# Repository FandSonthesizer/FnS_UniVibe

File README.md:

# FnS_UniVibe

A Univibe Clone using a white LED. This is a modern version of a univibe clone, instead of using a 15V lamp we use a white LED. This requested to modify the lamp driver circuit so now a dual opamp is driving it. We are using LDR03 for the light depending resistors, but a wide variety of LDRs will work too. Any standard Dual-Opamp will do.

The LDR's are so sensitive, that we have to dim the white LED quite a lot. A 47k resistor just brings the brightness down enough. Who would have thought... This should really bring down the power consumption compared to the original module.

Adapt the circuit to other LDR's by playing around with R58.

Check out our youtube channel: FatherandSonthesizer for a detailed demo of this cool module. (Though we use it in a synth rack...)

The PCB is prepared for the Vodoovibe and Resley Tone mod. Just do not populate C7, C12, C16 and C19. Instead follow the second link on the schematic and wire the caps on the 4P3T switch. connect using J12 and an 8pol cable. If you do not want the mod, ignore J12 and just populate the board as shown in the schematic.

Please note, that we forgot the true bypass switch on our front panel design. Maybe someone can come up with a better design, we would love to include it here.

The output signal of the module is somewhat less in volume than the input signal. A 2nd opamp takes care of that. A potentiometer on the front panel allows to adjust that volume.

For the led, LDR combination we created a symbol and a foot print for Kicad. Both are included in this repository. Make sure to configure your Kicad to make use of them. That symbol is called FnSVibeC, the foot print is in the NilsParts.pretty lib. Since no ambient light should reach the foto resistors we used a 3d-printer to print a housing for this part. Just a hollow square box, useing black PLA. (1mm wall)

The sound of this module is just awsome, make sure to check out youtube video. A guitar pedal version will follow later.

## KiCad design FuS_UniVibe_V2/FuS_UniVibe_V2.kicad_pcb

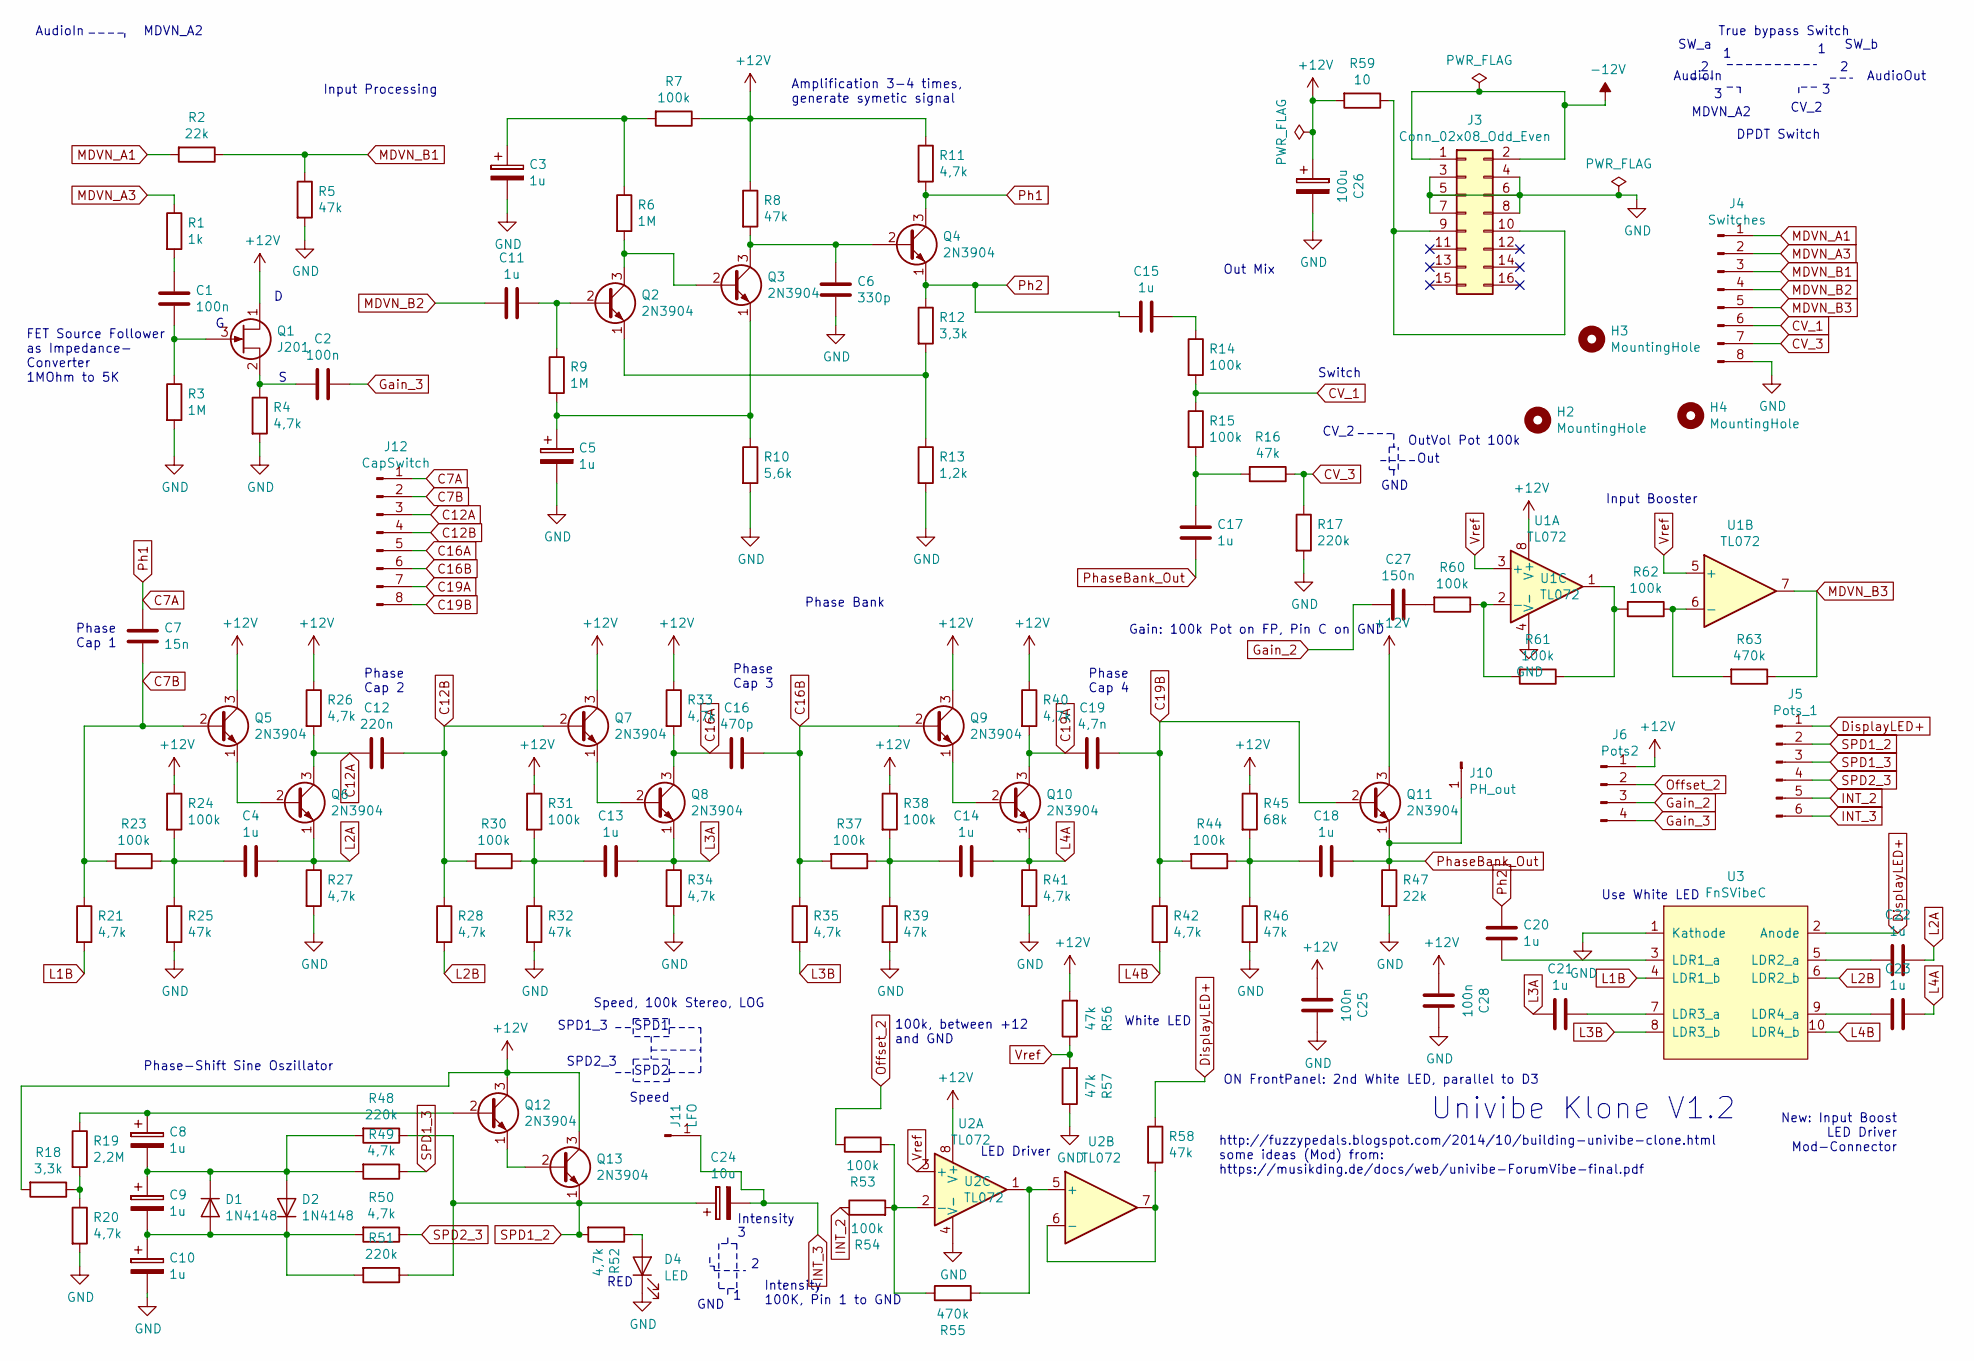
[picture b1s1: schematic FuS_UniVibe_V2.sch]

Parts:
C1, C2, C25, C28: 100n; Kondensator_Keramik
C3, C5, C8, C9, C10: 1u; Elko_D6.3mm_P2.50mm
C4, C11, C13, C14, C15, C17, C18, C20, C21, C22, C23: 1u; BIPolar_Elko_D6.3mm_P2.50mm
C6: 330p; Kondensator_Keramik
C7: 15n; Kondensator_Keramik
C12: 220n; Kondensator_Keramik
C16: 470p; Kondensator_Keramik
C19: 4,7n; Kondensator_Keramik
C24: 10u; Elko_D6.3mm_P2.50mm
C26: 100u; Elko_D6.3mm_P2.50mm
C27: 150n; Kondensator_Keramik
D1, D2: 1N4148; Diode_Horizontal
D4: LED; LED_Vertikal
H2, H3, H4: MountingHole; MountHole
J3: Conn_02x08_Odd_Even; PinHeader_2x08_P2.54mm_Vertical
J4: Switches; PinHeader_1x08_P2.54mm_Vertical
J5: Pots_1; PinHeader_1x06_P2.54mm_Vertical
J6: Pots2; PinHeader_1x04_P2.54mm_Vertical
J10: PH_out; Stift
J11: LFO; Stift
J12: CapSwitch; PinHeader_1x08_P2.54mm_Vertical
Q1: J201; TO-92_Wide
Q2, Q3, Q4, Q5, Q6, Q7, Q8, Q9, Q10, Q11, Q12, Q13: 2N3904; TO-92_Wide
R1: 1k; Widerstand_liegend
R2, R47: 22k; Widerstand_liegend
R3, R6, R9: 1M; Widerstand_liegend
R4, R11, R20, R21, R26, R27, R28, R33, R34, R35, R40, R41, R42, R49, R50, R52: 4,7k; Widerstand_liegend
R5, R8, R16, R25, R32, R39, R46, R56, R57, R58: 47k; Widerstand_liegend
R7, R14, R15, R23, R24, R30, R31, R37, R38, R44, R53, R54, R60, R61, R62: 100k; Widerstand_liegend
R10: 5,6k; Widerstand_liegend
R12, R18: 3,3k; Widerstand_liegend
R13: 1,2k; Widerstand_liegend
R17, R48, R51: 220k; Widerstand_liegend
R19: 2,2M; Widerstand_liegend
R45: 68k; Widerstand_liegend
R55, R63: 470k; Widerstand_liegend
R59: 10; Widerstand_liegend
U1, U2: TL072; DIP-8_W7.62mm_Socket_LongPads
U3: FnSVibeC; FnSVibe

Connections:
+12V: C25.2, C26.1, C28.2, J6.1, Q1.1 (D), Q5.3 (C), Q7.3 (C), Q9.3 (C), Q11.3 (C), Q12.3 (C), Q13.3 (C), R7.1, R8.1, R11.1, R18.2, R24.1, R26.1, R31.1, R33.1, R38.1, R40.1, R45.1, R56.2, R59.2, U1.8 (V+), U2.8 (V+)
-12V: J3.1, J3.2
C7A: C7.1, J12.1, Q4.3 (C), R11.2
C7B: C7.2, J12.2, Q5.2 (B), R21.1, R23.2
C12A: C12.2, J12.3, Q6.3 (C), R26.2
C12B: C12.1, J12.4, Q7.2 (B), R28.1, R30.2
C16A: C16.2, J12.5, Q8.3 (C), R33.2
C16B: C16.1, J12.6, Q9.2 (B), R35.1, R37.2
C19A: C19.2, J12.7, Q10.3 (C), R40.2
C19B: C19.1, J12.8, Q11.2 (B), R42.1, R44.2
CV_1: J4.6, R14.2, R15.1
CV_3: J4.7, R16.1, R17.1
DisplayLED+: J5.1, R58.1, U3.2 (Anode)
GND: C3.2, C5.2, C6.2, C10.2, C25.1, C26.2, C28.1, D4.1 (K), J3.3, J3.4, J3.5, J3.6, J3.7, J3.8, J4.8, R3.2, R4.2, R5.2, R10.2, R13.2, R17.2, R20.2, R25.2, R27.2, R32.2, R34.2, R39.2, R41.2, R46.2, R47.2, R57.1, U1.4 (V-), U2.4 (V-), U3.1 (Kathode)
Gain_2: C27.2, J6.3
Gain_3: C2.1, J6.4
INT_2: J5.5, R54.1
INT_3: C24.2, J5.6, J11.1
L1B: R21.2, U3.4 (LDR1_b)
L2A: C4.1, C22.2, Q6.1 (E), R27.1
L2B: R28.2, U3.6 (LDR2_b)
L3A: C13.1, C21.1, Q8.1 (E), R34.1
L3B: R35.2, U3.8 (LDR3_b)
L4A: C14.1, C23.2, Q10.1 (E), R41.1
L4B: R42.2, U3.10 (LDR4_b)
MDVN_A1: J4.1, R2.2
MDVN_A3: J4.2, R1.1
MDVN_B1: J4.3, R2.1, R5.1
MDVN_B2: C11.2, J4.4
MDVN_B3: J4.5, R63.1, U1.7
unnamed: C1.1, R1.2
unnamed: C1.2, Q1.3 (G), R3.1
unnamed: C2.2, Q1.2 (S), R4.1
unnamed: C3.1, R6.1, R7.2
unnamed: C4.2, R23.1, R24.2, R25.1
unnamed: C5.1, Q3.1 (E), R9.2, R10.1
unnamed: C6.1, Q3.3 (C), Q4.2 (B), R8.2
unnamed: C8.1, Q12.2 (B), R19.1
unnamed: C8.2, C9.1, D1.1 (K), D2.2 (A), R48.2, R49.2
unnamed: C9.2, C10.1, D1.2 (A), D2.1 (K), R50.2, R51.2
unnamed: C11.1, Q2.2 (B), R9.1
unnamed: C13.2, R30.1, R31.2, R32.1
unnamed: C14.2, R37.1, R38.2, R39.1
unnamed: C15.1, R14.1
unnamed: C17.2, R15.2, R16.2
unnamed: C18.2, R44.1, R45.2, R46.1
unnamed: C20.1, U3.3 (LDR1_a)
unnamed: C21.2, U3.7 (LDR3_a)
unnamed: C22.1, U3.5 (LDR2_a)
unnamed: C23.1, U3.9 (LDR4_a)
unnamed: C27.1, R60.2
unnamed: D4.2 (A), R52.1
unnamed: J3.9, J3.10, R59.1
unnamed: Q2.1 (E), R12.2, R13.1
unnamed: Q2.3 (C), Q3.2 (B), R6.2
unnamed: Q5.1 (E), Q6.2 (B)
unnamed: Q7.1 (E), Q8.2 (B)
unnamed: Q9.1 (E), Q10.2 (B)
unnamed: Q12.1 (E), Q13.2 (B)
unnamed: R18.1, R19.2, R20.1
unnamed: R53.2, R54.2, R55.1, U2.2 (-)
unnamed: R55.2, U2.1, U2.5 (+)
unnamed: R58.2, U2.6 (-), U2.7
unnamed: R60.1, R61.2, U1.2 (-)
unnamed: R61.1, R62.2, U1.1
unnamed: R62.1, R63.2, U1.6 (-)
Offset_2: J6.2, R53.1
Ph2: C15.2, C20.2, Q4.1 (E), R12.1
PhaseBank_Out: C17.1, C18.1, J10.1, Q11.1 (E), R47.1
SPD1_2: C24.1, J5.2, Q13.1 (E), R48.1, R51.1, R52.2
SPD1_3: J5.3, R49.1
SPD2_3: J5.4, R50.1
Vref: R56.1, R57.2, U1.3 (+), U1.5 (+), U2.3 (+)

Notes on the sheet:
AudioIn
MDVN_A2
CV_2
GND
Out
OutVol Pot 100k
Input Processing
Out Mix
Phase Bank
Phase-Shift Sine Oszillator
SPD1
SPD2
SPD1_3
SPD2_3
Speed, 100k Stereo, LOG
Intensity 100K, Pin 1 to GND
Switch
Univibe Klone V1.2
http://fuzzypedals.blogspot.com/2014/10/building-univibe-clone.html some ideas (Mod) from: https://musikding.de/docs/web/univibe-ForumVibe-final.pdf
White LED
Speed
FET Source Follower as Impedance- Converter 1MOhm to 5K
Amplification 3-4 times, generate symetic signal
Phase Cap 1
Phase Cap 2
Phase Cap 3
Phase Cap 4
Intensity
100k, between +12 and GND
ON FrontPanel: 2nd White LED, parallel to D3
RED
True bypass Switch
SW_a
SW_b
DPDT Switch
AudioOut
Input Booster
Gain: 100k Pot on FP, Pin C on GND
New: Input Boost LED Driver Mod-Connector
LED Driver

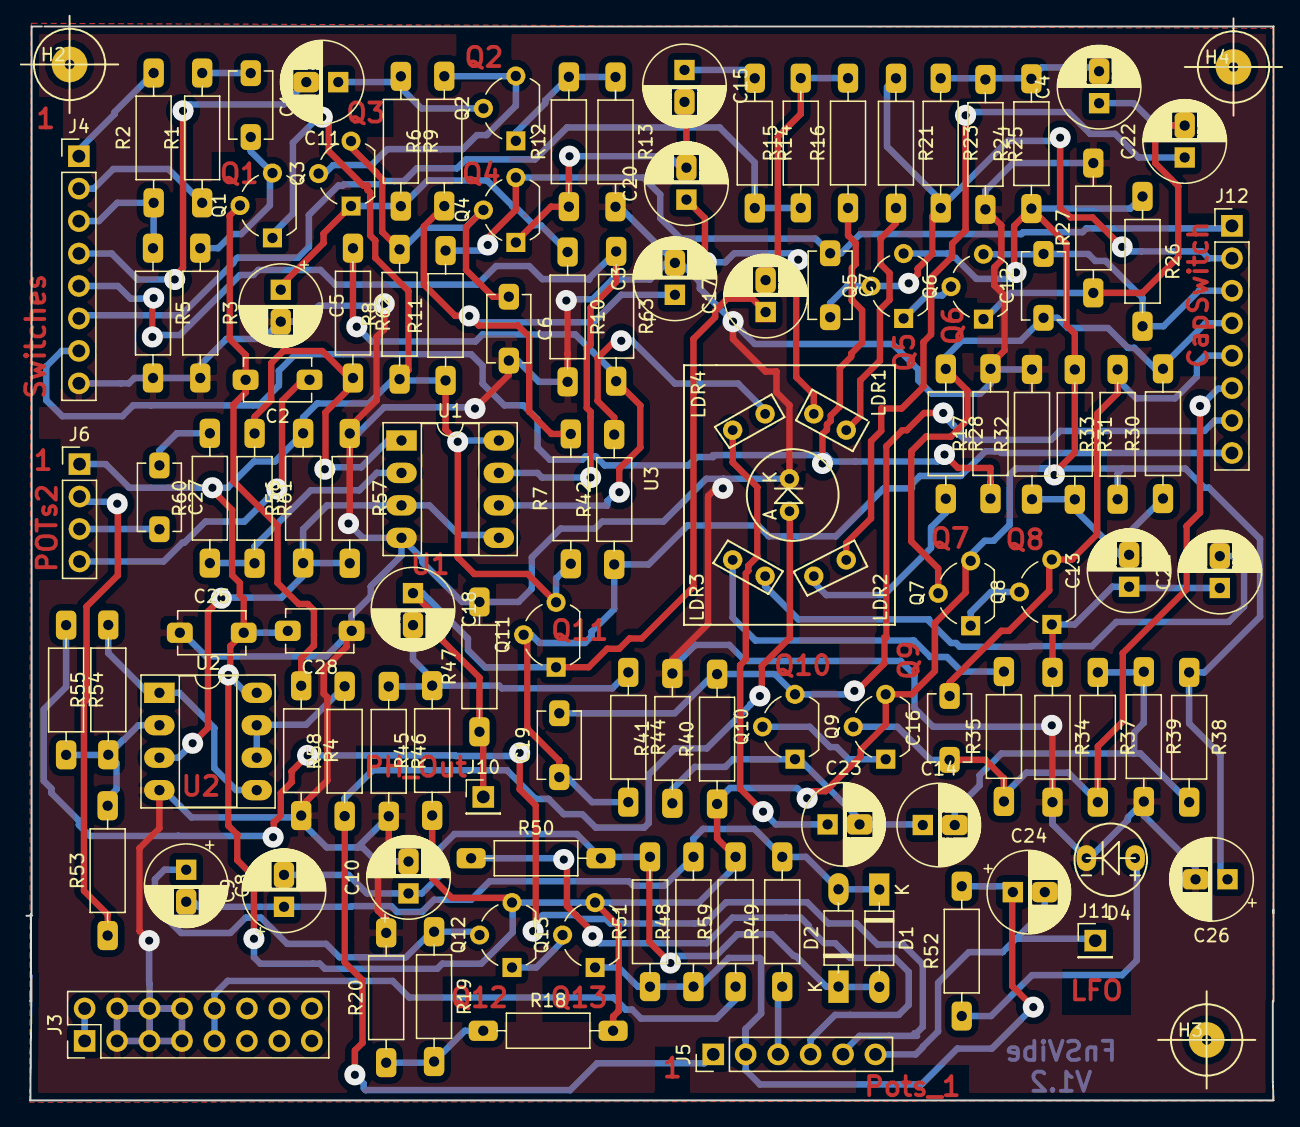
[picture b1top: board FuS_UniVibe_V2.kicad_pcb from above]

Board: 2 copper layers, 97.6 x 84.0 mm, 116 parts (0 on the bottom side), 73 nets.
